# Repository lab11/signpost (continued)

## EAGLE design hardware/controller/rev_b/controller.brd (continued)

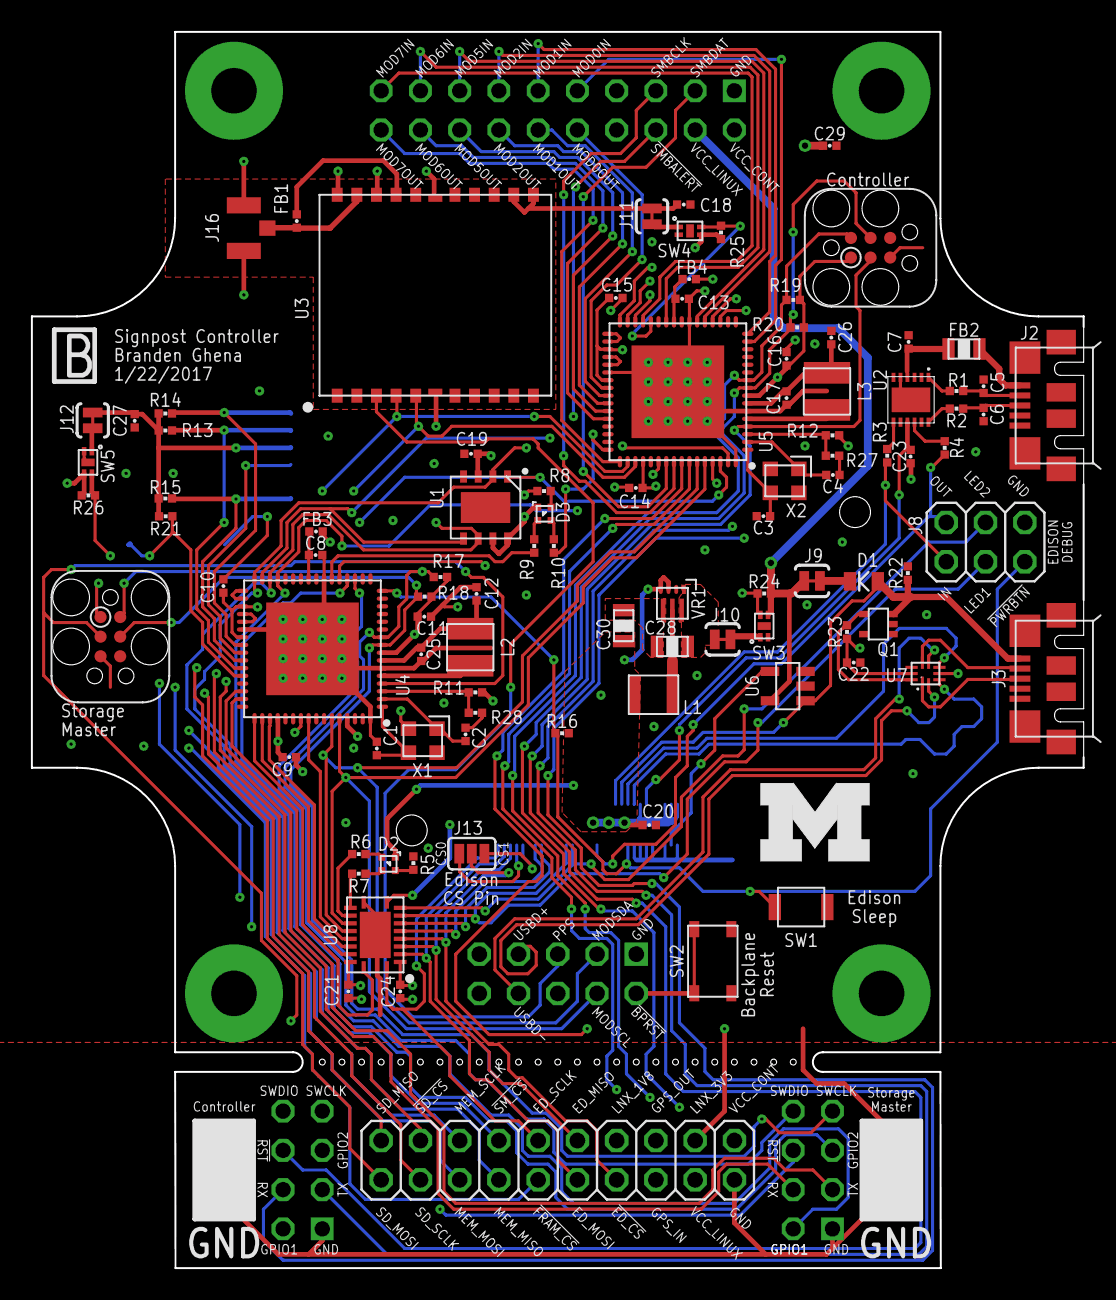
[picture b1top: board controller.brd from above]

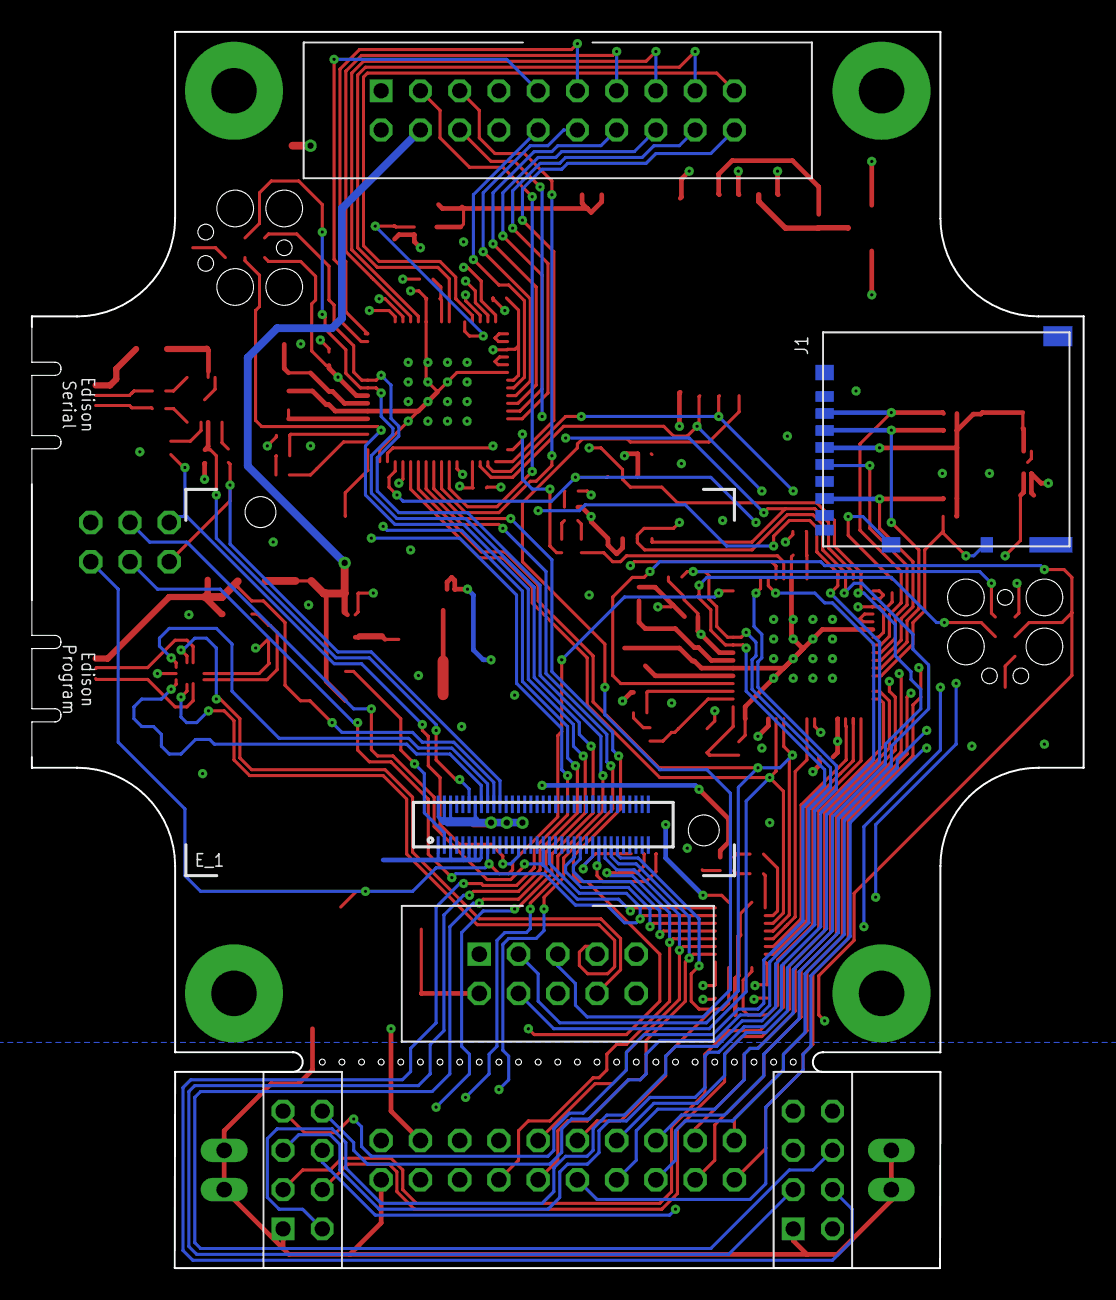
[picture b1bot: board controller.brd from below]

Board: 4 copper layers, 68.1 x 80.0 mm, 103 parts (2 on the bottom side), 123 nets.

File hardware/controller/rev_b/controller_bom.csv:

"# Bill of Materials",,,,,,,,,
"# Converted from controller_bom.xls",,,,,,,,,
"# Generated by bom_to_text.py",,,,,,,,,
"#",,,,,,,,,
Qty,Value,Device,Package,Parts,Description,AMAZON,DIGIKEY,MOUSER,NEWARK
4,8pF,CAPACITOR0402_CAP,0402_CAP,"C1, C2, C3, C4",0402 Capacitor,,490-8230-1-ND,,
2,47pF,CAPACITOR0402_CAP,0402_CAP,"C5, C6",0402 Capacitor,,490-6241-1-ND,,
1,10nF,CAPACITOR0402_CAP,0402_CAP,C7,0402 Capacitor,,490-6296-1-ND,,
17,100nF,CAPACITOR0402_CAP,0402_CAP,"C8, C9, C10, C11, C12, C13, C14, C15, C16, C17, C18, C19, C20, C21, C22, C23, C24",0402 Capacitor,,490-10777-1-ND,,
3,4.7uF,CAPACITOR0402_CAP,0402_CAP,"C25, C26, C27",0402 Capacitor,,490-13252-1-ND,,
1,10uF,CAPACITOR0805_CAP,0805_CAP,C28,0402 Capacitor,,490-8316-1-ND,,
1,10uF,CAPACITOR0402_CAP,0402_CAP,C29,0402 Capacitor,,490-13811-1-ND,,
1,22uF,CAPACITOR0805_CAP,0805_CAP,C30,0402 Capacitor,,490-1719-1-ND,,
1,DIODE,DIODE,0805_DIODE,D1,,,478-7800-1-ND,,
2,SML-LX0404SIUPGUSB,SML-LX0404SIUPGUSB,1MM_SQ_4PAD,"D2, D3",1mm^2 RGB LED,,67-2125-1-ND,,
1,EDISON_CONNECTOR_SEGMENTED,EDISON_CONNECTOR_SEGMENTED,EDISON_DAUGHTER,E_1,,B00PTVSS4A,,798-DF40HC3070DS4V51,
1,300,FERRITE_BEAD0402,0402_CAP,FB1,,,ACML-0402-301-TCT-ND,,
1,600,FERRITE_BEAD0805,0805_CAP,FB2,,,240-2390-1-ND,,
1,1.5k,FERRITE_BEAD0402,0402_CAP,FB3,,,1276-6395-1-ND,,
1,1.5k,FERRITE_BEAD0402,0402_CAP,FB4,,,1276-6395-1-ND,,
1,DM3AT-SF-PEJM5,DM3AT-SF-PEJM5,DM3AT-SF-PEJM5,J1,CONN MICRO SD R/A PUSH-PUSH SMD,,HR1964CT-ND,,
2,MICRO_USB_B_HIROSE_ZX62R-B-5P,MICRO_USB_B_HIROSE_ZX62R-B-5P,USB_MICRO_B-HIROSE-ZX62R-B-5P,"J2, J3",USB Micro B Connector,,H125274CT-ND,,
1,MODULE_CONTROLLER,MODULE_CONTROLLER,MODULE_CONTROLLER,J4,Controller module for signpost,,"S9172-ND , S9169-ND , S2221EC-04-ND , S2221EC-04-ND",,
2,,PINHD-1X2,1X02,"J5, J6",PIN HEADER,,,,
1,,PINHD-2X10,2X10,J7,PIN HEADER,,,,
1,,PINHD-2X3,2X03,J8,PIN HEADER,,,,
4,SOLDERJUMPERTRACE,SOLDERJUMPERTRACE,SJ_2S-TRACE,"J9, J10, J11, J12",Solder Jumper,,,,
1,,SOLDERJUMPER_2WAYPASTE2&3,SJ_3_PASTE2&3,J13,Solder Jumper,,,,
2,TC2030-JLINK-L,TC2030-JLINK-L,TC2030-IDC,"J14, J15",,,,,
1,U.FL-R-SMT,U.FL-R-SMT,U.FL_SMT,J16,U.FL-R-SMT Antenna Connector,,H122041-ND,,
1,0.47uH,INDUCTORDFE322512C,DFE322512C,L1,A very specific inductor,,490-10596-1-ND,81-1277AS-H-R47MP2,
1,22uH,LHQ3NP,1212,L2,LHQ3NP Inductor,,490-5350-1-ND,,
1,22uH,LHQ3NP,1212,L3,LHQ3NP Inductor,,490-5350-1-ND,,
1,UMICH_SOLID_MEDIUM,UMICH_SOLID_MEDIUM,UMICH_SOLID_200MIL,LOGO1,,,,,
1,DMN32D2LDF,DMN32D2LDF,SOT353,Q1,Common source dual n-channel mosfet,,DMN32D2LDF-7DICT-ND,,
2,27,RESISTOR0402_RES,0402_RES,"R1, R2",Resistor,,1276-3907-1-ND,,
2,100,RESISTOR0402_RES,0402_RES,"R3, R4",Resistor,,1276-3429-1-ND,,
6,1k,RESISTOR0402_RES,0402_RES,"R5, R6, R7, R8, R9, R10",Resistor,,1276-3430-1-ND,,
6,10k,RESISTOR0402_RES,0402_RES,"R11, R12, R13, R14, R15, R16",Resistor,,1276-3431-1-ND,,
5,100k,RESISTOR0402_RES,0402_RES,"R17, R18, R19, R20, R21, R22, R23",Resistor,,1276-3432-1-ND,,
3,1M,RESISTOR0402_RES,0402_RES,"R24, R25, R26",Resistor,,1276-3433-1-ND,,
2,DNP,RESISTOR0402_RES,0402_RES,"R27, R28",Resistor,,1276-3431-1-ND,,
1,B3U-1000P,B3U-1000P,B3U-1000P,SW1,Switch,,SW1020CT-ND,,
1,PTS810SJ,PTS810SJ,PTS810SJ,SW2,PTS810SJ Push Button Switch,,CKN10504CT-ND,,
3,SIP3240X,SIP3240X,TDFN4,"SW3, SW4, SW5",High power (2.4 A) high-side switch,,SIP32402ADNP-T1GE4CT-ND,,
1,FM25CLXXB-DG,FM25CLXXB-DG,TDFN-8,U1,Cypress FRAM,,FM25CL64B-DGRA-ND,,
1,FTDI234XD,FTDI234XD,DFN-12/3MM,U2,FTDI234XD USB to UART Bridge in 3x3 DFN Package,,768-1178-1-ND,895-FT234XD-R,53X3171
1,RXM-GPS-RM-T,RXM-GPS-RM-T,RXM-GPS-RM-T,U3,The RM Series GPS receiver module is a,,RXM-GPS-RM-TCT-ND,,
2,SAM4LC8BA,SAM4LC8BA,QFN-64-9MM,"U4, U5",SAM4L Microcontroller. 64QFN Package. 512 Flash.,,ATSAM4LC8BA-MURCT-ND,,
1,SN74LVC1G125DBVR,SN74LVC1G125DBVR,SOT-23-5,U6,Single Bus Buffer Gate with 3-state output,,296-11603-1-nd,,
1,TS3USB30E,TS3USB30E,UQFN-10,U7,USB Mux with OE control and ESD,,296-24684-1-ND,,
1,TXS0108EVQFN20,TXS0108EVQFN20,R-PVQFN-N20,U8,TXS0108E 8-Bit Bi-directional Voltage Translator,,296-24806-1-ND,,
1,TPS62086,TPS62086,RLT0007A,VR1,Buck Switching Regulator IC Positive Fixed 3.3V 1 Output 3A 7-VFDFN,,296-40831-1-ND,,
2,16MHz,FH1600015,FHXXX,"X1, X2",Pericom Type FH 16 MHz 2.5 x 2.0 mm,,FH1600015CT-ND,,

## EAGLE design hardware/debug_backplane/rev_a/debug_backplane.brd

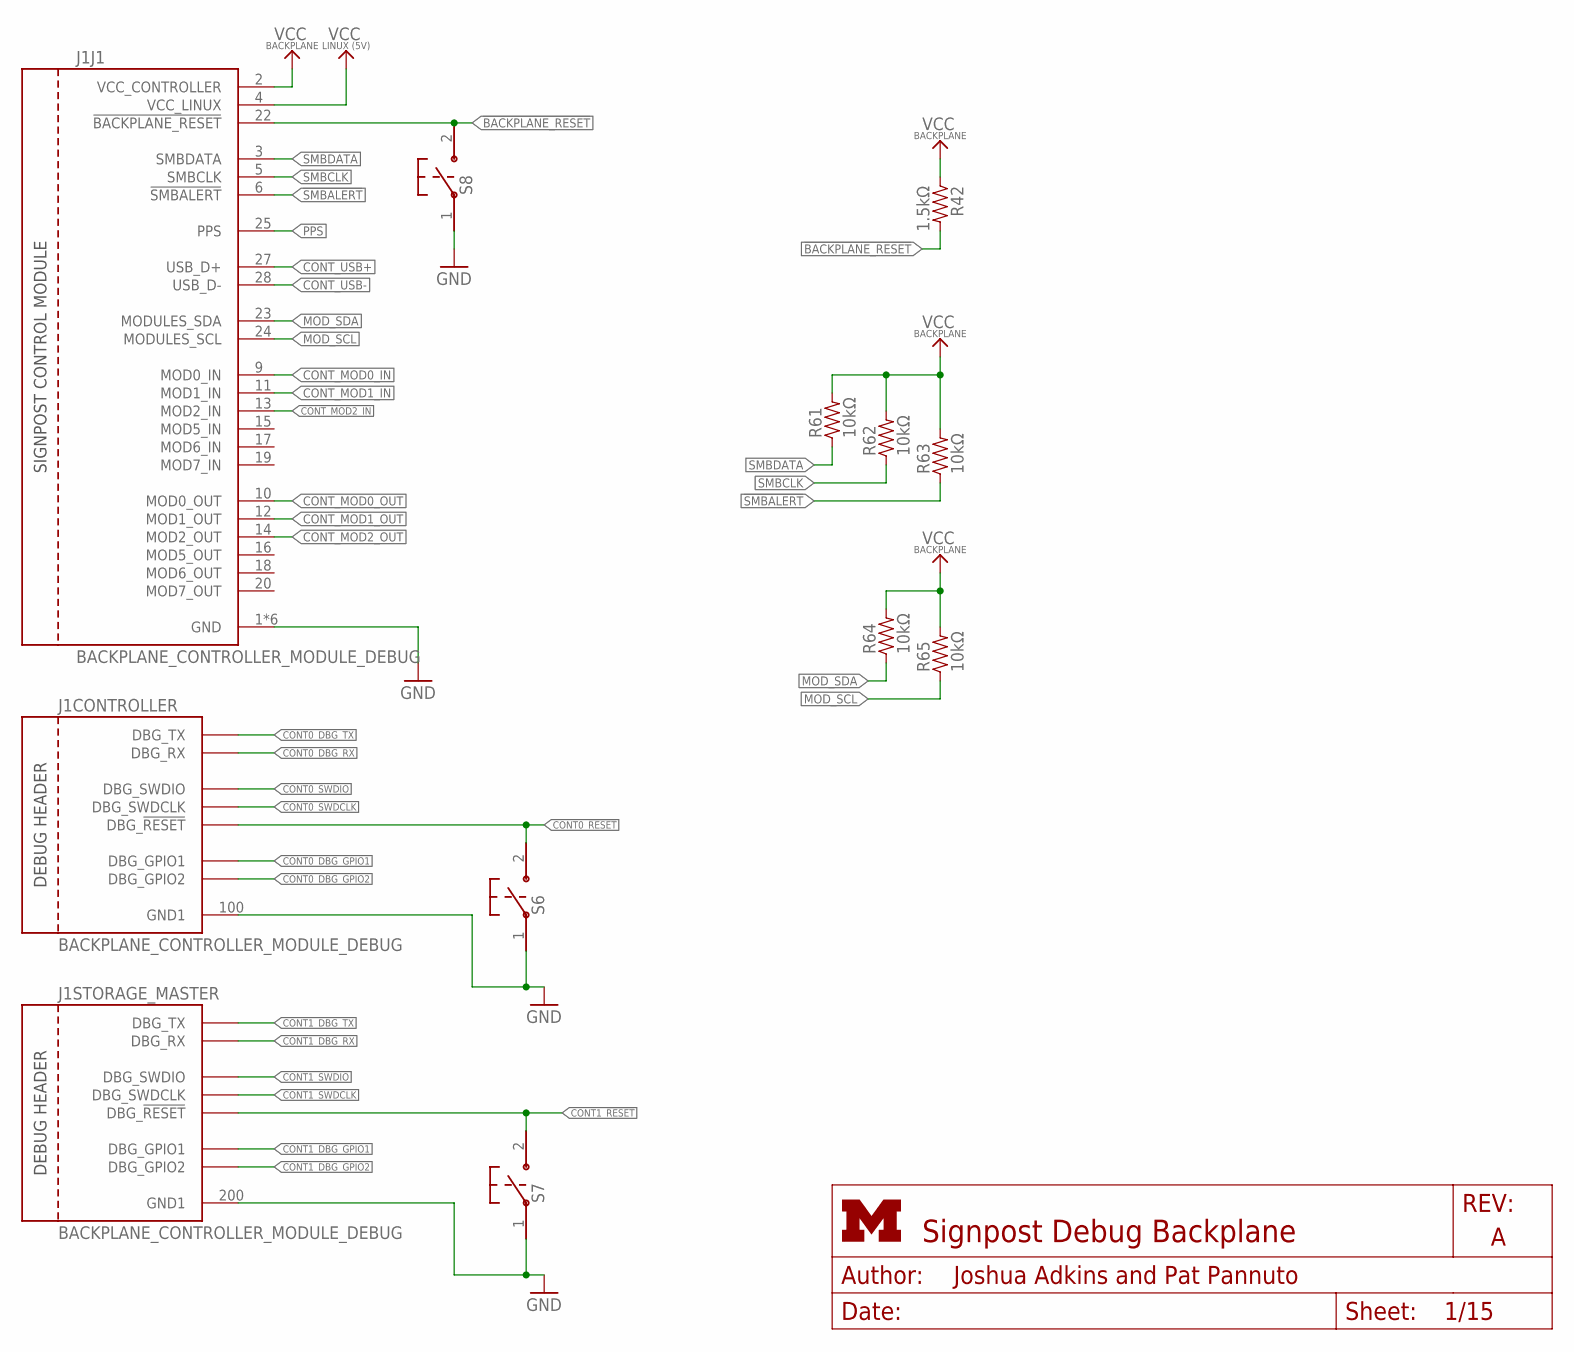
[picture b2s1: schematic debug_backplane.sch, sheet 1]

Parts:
J1: BACKPLANE_CONTROLLER_MODULE_DEBUG; BACKPLANE_MODULE_20PIN_10PIN_DEBUG
R42: 1.5kΩ; 0603-RES
R61, R62, R63, R64, R65: 10kΩ; 0603-RES
S6, S7, S8: B3U-1000P

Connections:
!BACKPLANE_RESET: J1.22 (!BACKPLANE_RESET), R42.2, S8.2; also elsewhere on the board
!SMBALERT: J1.6 (!SMBALERT), R63.1; also elsewhere on the board
CONT0_!RESET: J1.105 (DBG_!RESET), S6.2; also elsewhere on the board
CONT0_DBG_GPIO1: J1.101 (DBG_GPIO1); also elsewhere on the board
CONT0_DBG_GPIO2: J1.104 (DBG_GPIO2); also elsewhere on the board
CONT0_DBG_RX: J1.103 (DBG_RX); also elsewhere on the board
CONT0_DBG_TX: J1.102 (DBG_TX); also elsewhere on the board
CONT0_SWDCLK: J1.106 (DBG_SWDCLK); also elsewhere on the board
CONT0_SWDIO: J1.107 (DBG_SWDIO); also elsewhere on the board
CONT1_!RESET: J1.205 (DBG_!RESET), S7.2; also elsewhere on the board
CONT1_DBG_GPIO1: J1.201 (DBG_GPIO1); also elsewhere on the board
CONT1_DBG_GPIO2: J1.204 (DBG_GPIO2); also elsewhere on the board
CONT1_DBG_RX: J1.203 (DBG_RX); also elsewhere on the board
CONT1_DBG_TX: J1.202 (DBG_TX); also elsewhere on the board
CONT1_SWDCLK: J1.206 (DBG_SWDCLK); also elsewhere on the board
CONT1_SWDIO: J1.207 (DBG_SWDIO); also elsewhere on the board
CONT_MOD0_IN: J1.9 (MOD0_IN); also elsewhere on the board
CONT_MOD0_OUT: J1.10 (MOD0_OUT); also elsewhere on the board
CONT_MOD1_IN: J1.11 (MOD1_IN); also elsewhere on the board
CONT_MOD1_OUT: J1.12 (MOD1_OUT); also elsewhere on the board
CONT_MOD2_IN: J1.13 (MOD2_IN); also elsewhere on the board
CONT_MOD2_OUT: J1.14 (MOD2_OUT); also elsewhere on the board
CONT_USB+: J1.27 (USB_D+); also elsewhere on the board
CONT_USB-: J1.28 (USB_D-); also elsewhere on the board
GND: J1.1 (GND), J1.21 (GND), J1.100 (GND1), J1.200 (GND1), J1.MNT1 (GND), J1.MNT2 (GND), J1.MNT3 (GND), J1.MNT4 (GND), S6.1, S7.1, S8.1; also elsewhere on the board
MOD_SCL: J1.24 (MODULES_SCL), R65.1; also elsewhere on the board
MOD_SDA: J1.23 (MODULES_SDA), R64.1; also elsewhere on the board
PPS: J1.25 (PPS); also elsewhere on the board
SMBCLK: J1.5 (SMBCLK), R62.1; also elsewhere on the board
SMBDATA: J1.3 (SMBDATA), R61.1; also elsewhere on the board
VCC_BACKPLANE: J1.2 (VCC_CONTROLLER), R42.1, R61.2, R62.2, R63.2, R64.2, R65.2; also elsewhere on the board
VCC_LINUX: J1.4 (VCC_LINUX); also elsewhere on the board

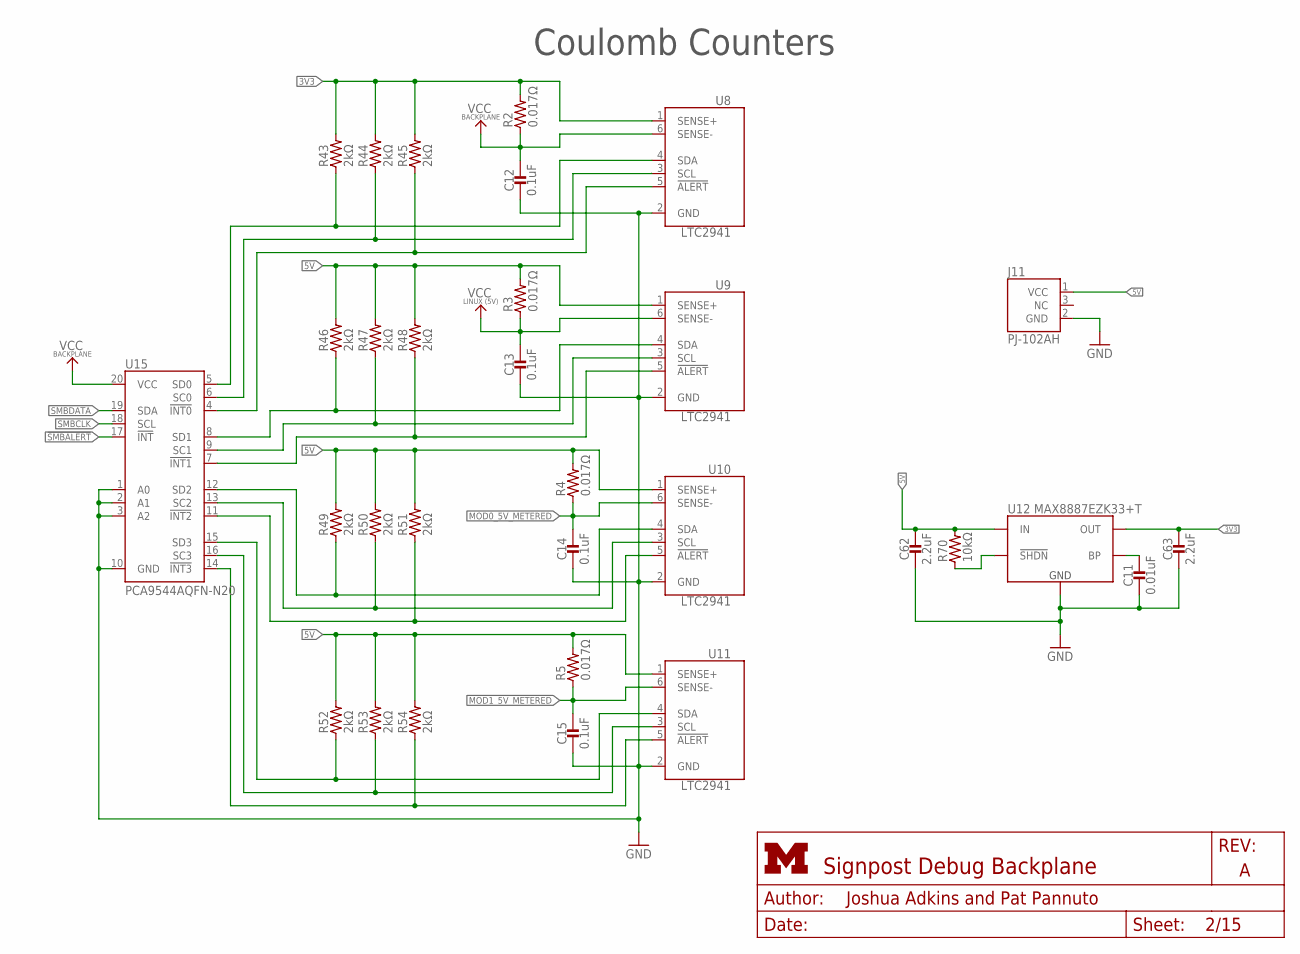
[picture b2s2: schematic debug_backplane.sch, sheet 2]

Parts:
C11: 0.01uF; 0402_CAP
C12, C13, C14, C15: 0.1uF; 0402_CAP
C62, C63: 2.2uF; 0603_CAP
J11: PJ-102AH
R2, R3, R4, R5: 0.017Ω; 0805_RES
R43, R44, R45, R46, R47, R48, R49, R50, R51, R52, R53, R54: 2kΩ; 0402_RES
R70: 10kΩ; 0603-RES
U8, U9, U10, U11: LTC2941; DFN-6-2MMX3MM
U12: MAX8887EZK33+T; SOT-23-5
U15: PCA9544AQFN-N20; QFN-N20

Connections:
3V3: C63.1, R2.2, R43.2, R44.2, R45.2, U8.1 (SENSE+), U12.5 (OUT); also elsewhere on the board
5V: C62.1, J11.1 (VCC), R3.2, R4.2, R5.2, R46.2, R47.2, R48.2, R49.2, R50.2, R51.2, R52.2, R53.2, R54.2, R70.2, U9.1 (SENSE+), U10.1 (SENSE+), U11.1 (SENSE+), U12.1 (IN); also elsewhere on the board
!SMBALERT: U15.17 (!INT); also elsewhere on the board
GND: C11.2, C12.2, C13.2, C14.2, C15.2, C62.2, C63.2, J11.2 (GND), U8.2 (GND), U9.2 (GND), U10.2 (GND), U11.2 (GND), U12.2 (GND), U15.1 (A0), U15.2 (A1), U15.3 (A2), U15.10 (GND); also elsewhere on the board
MOD0_5V_METERED: C14.1, R4.1, U10.6 (SENSE-); also elsewhere on the board
MOD1_5V_METERED: C15.1, R5.1, U11.6 (SENSE-); also elsewhere on the board
unnamed: R70.1, U12.3 (!SHDN)
unnamed: C11.1, U12.4 (BP)
unnamed: R43.1, U8.4 (SDA), U15.5 (SD0)
unnamed: R44.1, U8.3 (SCL), U15.6 (SC0)
unnamed: R49.1, U10.4 (SDA), U15.12 (SD2)
unnamed: R50.1, U10.3 (SCL), U15.13 (SC2)
unnamed: R51.1, U10.5 (!ALERT), U15.11 (!INT2)
unnamed: R52.1, U11.4 (SDA), U15.15 (SD3)
unnamed: R53.1, U11.3 (SCL), U15.16 (SC3)
unnamed: R54.1, U11.5 (!ALERT), U15.14 (!INT3)
unnamed: R45.1, U8.5 (!ALERT), U15.4 (!INT0)
unnamed: R46.1, U9.4 (SDA), U15.8 (SD1)
unnamed: R47.1, U9.3 (SCL), U15.9 (SC1)
unnamed: R48.1, U9.5 (!ALERT), U15.7 (!INT1)
SMBCLK: U15.18 (SCL); also elsewhere on the board
SMBDATA: U15.19 (SDA); also elsewhere on the board
VCC_BACKPLANE: C12.1, R2.1, U8.6 (SENSE-), U15.20 (VCC); also elsewhere on the board
VCC_LINUX: C13.1, R3.1, U9.6 (SENSE-); also elsewhere on the board

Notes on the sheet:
Coulomb Counters

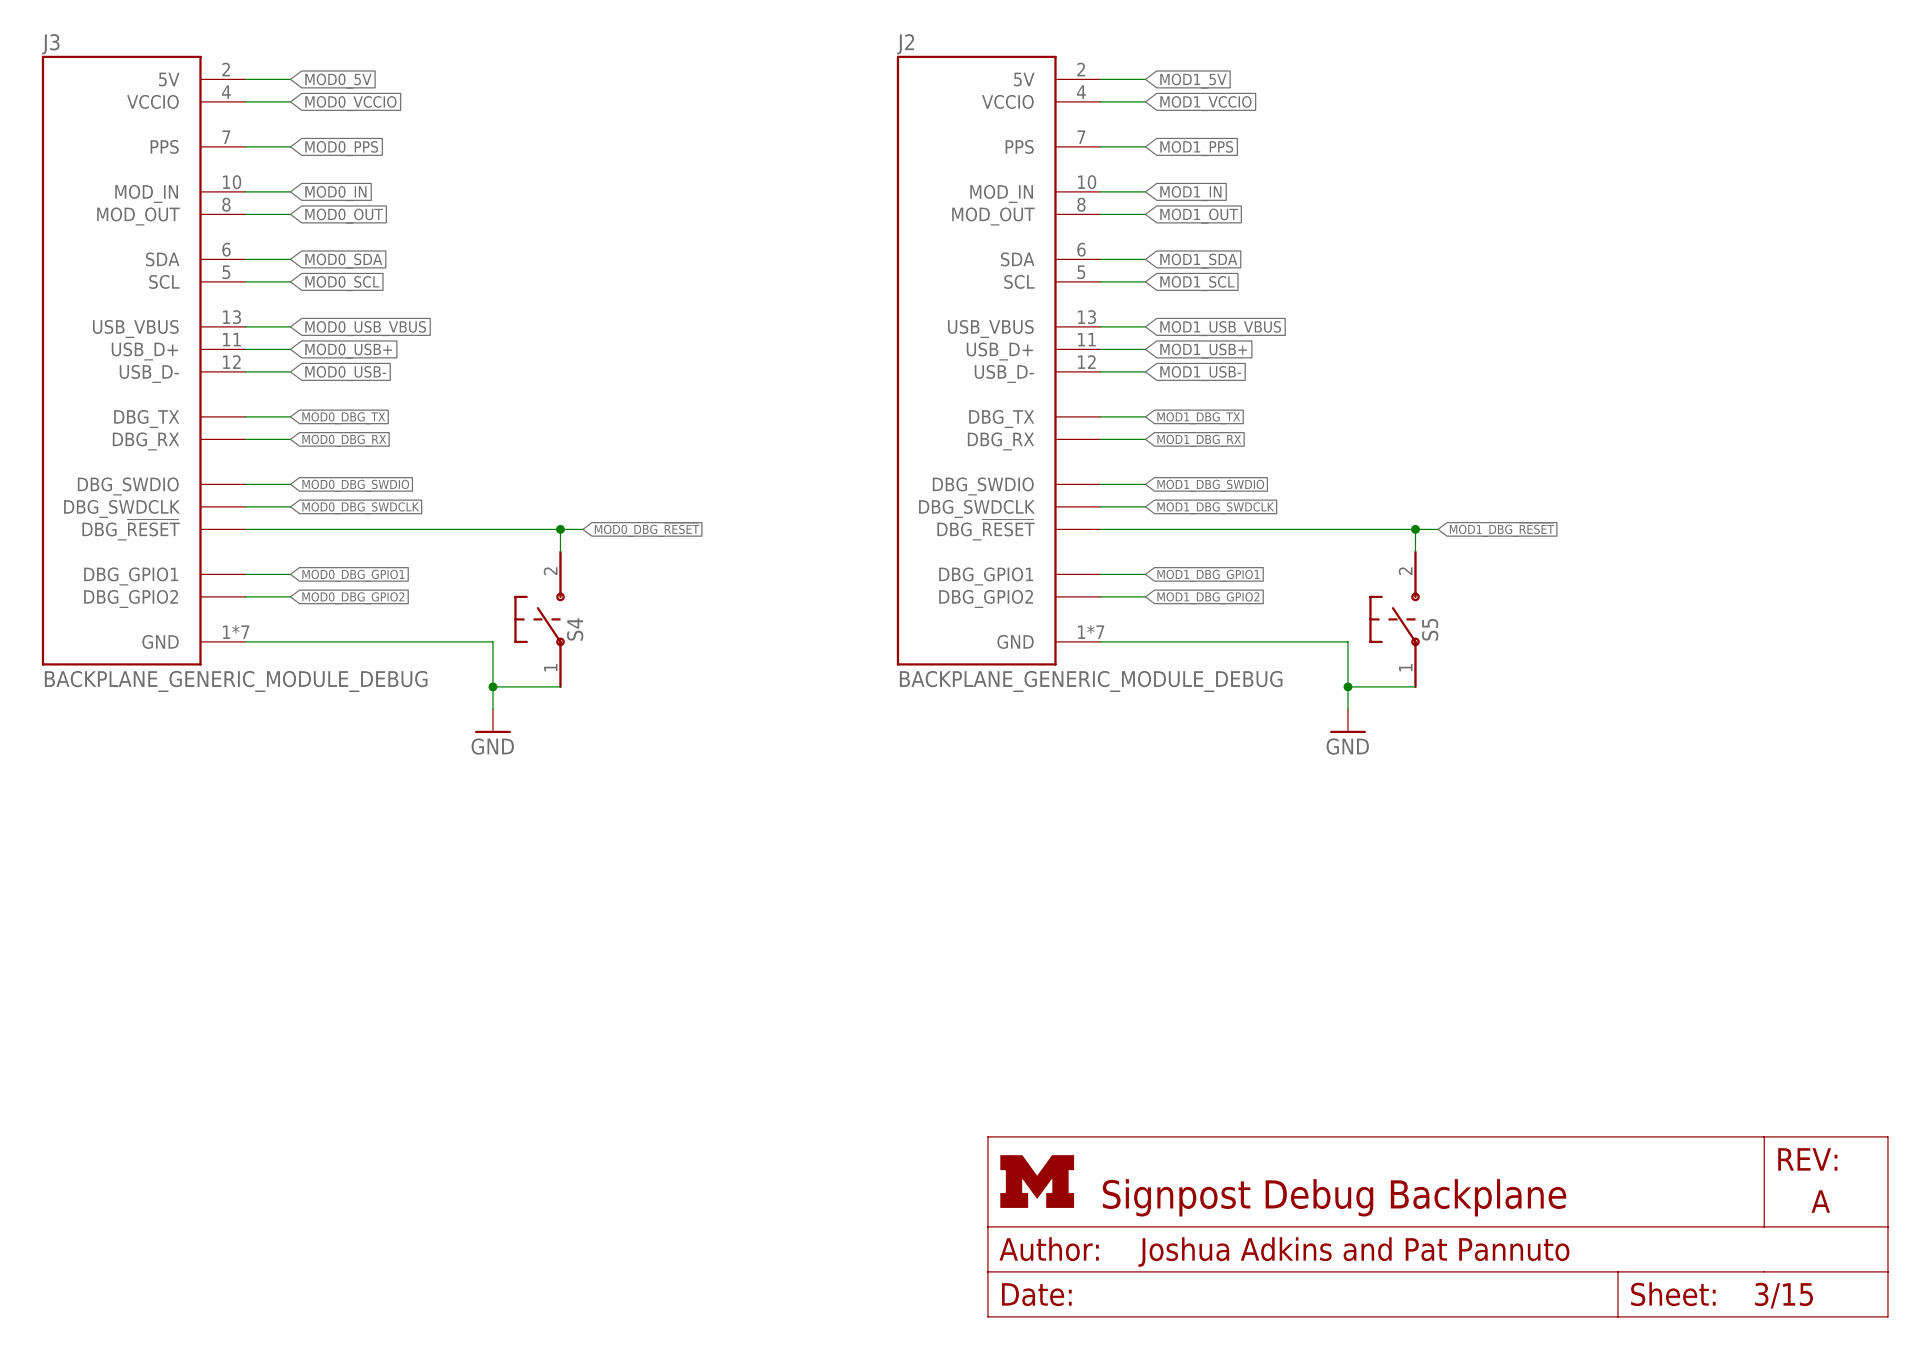
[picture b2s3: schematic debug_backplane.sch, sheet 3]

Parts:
J2, J3: BACKPLANE_GENERIC_MODULE_DEBUG; BACKPLANE_MODULE_14PIN_8PIN
S4, S5: B3U-1000P

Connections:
GND: J2.1 (GND), J2.14 (GND), J2.15 (GND), J2.MNT1 (GND), J2.MNT2 (GND), J2.MNT3 (GND), J2.MNT4 (GND), J3.1 (GND), J3.14 (GND), J3.15 (GND), J3.MNT1 (GND), J3.MNT2 (GND), J3.MNT3 (GND), J3.MNT4 (GND), S4.1, S5.1; also elsewhere on the board
MOD0_5V: J3.2 (5V); also elsewhere on the board
MOD0_DBG_!RESET: J3.20 (DBG_!RESET), S4.2; also elsewhere on the board
MOD0_DBG_GPIO1: J3.16 (DBG_GPIO1); also elsewhere on the board
MOD0_DBG_GPIO2: J3.19 (DBG_GPIO2); also elsewhere on the board
MOD0_DBG_RX: J3.18 (DBG_RX); also elsewhere on the board
MOD0_DBG_SWDCLK: J3.21 (DBG_SWDCLK); also elsewhere on the board
MOD0_DBG_SWDIO: J3.22 (DBG_SWDIO); also elsewhere on the board
MOD0_DBG_TX: J3.17 (DBG_TX); also elsewhere on the board
MOD0_IN: J3.10 (MOD_IN); also elsewhere on the board
MOD0_OUT: J3.8 (MOD_OUT); also elsewhere on the board
MOD0_PPS: J3.7 (PPS); also elsewhere on the board
MOD0_SCL: J3.5 (SCL); also elsewhere on the board
MOD0_SDA: J3.6 (SDA); also elsewhere on the board
MOD0_USB+: J3.11 (USB_D+); also elsewhere on the board
MOD0_USB-: J3.12 (USB_D-); also elsewhere on the board
MOD0_USB_VBUS: J3.13 (USB_VBUS); also elsewhere on the board
MOD0_VCCIO: J3.4 (VCCIO); also elsewhere on the board
MOD1_5V: J2.2 (5V); also elsewhere on the board
MOD1_DBG_!RESET: J2.20 (DBG_!RESET), S5.2; also elsewhere on the board
MOD1_DBG_GPIO1: J2.16 (DBG_GPIO1); also elsewhere on the board
MOD1_DBG_GPIO2: J2.19 (DBG_GPIO2); also elsewhere on the board
MOD1_DBG_RX: J2.18 (DBG_RX); also elsewhere on the board
MOD1_DBG_SWDCLK: J2.21 (DBG_SWDCLK); also elsewhere on the board
MOD1_DBG_SWDIO: J2.22 (DBG_SWDIO); also elsewhere on the board
MOD1_DBG_TX: J2.17 (DBG_TX); also elsewhere on the board
MOD1_IN: J2.10 (MOD_IN); also elsewhere on the board
MOD1_OUT: J2.8 (MOD_OUT); also elsewhere on the board
MOD1_PPS: J2.7 (PPS); also elsewhere on the board
MOD1_SCL: J2.5 (SCL); also elsewhere on the board
MOD1_SDA: J2.6 (SDA); also elsewhere on the board
MOD1_USB+: J2.11 (USB_D+); also elsewhere on the board
MOD1_USB-: J2.12 (USB_D-); also elsewhere on the board
MOD1_USB_VBUS: J2.13 (USB_VBUS); also elsewhere on the board
MOD1_VCCIO: J2.4 (VCCIO); also elsewhere on the board

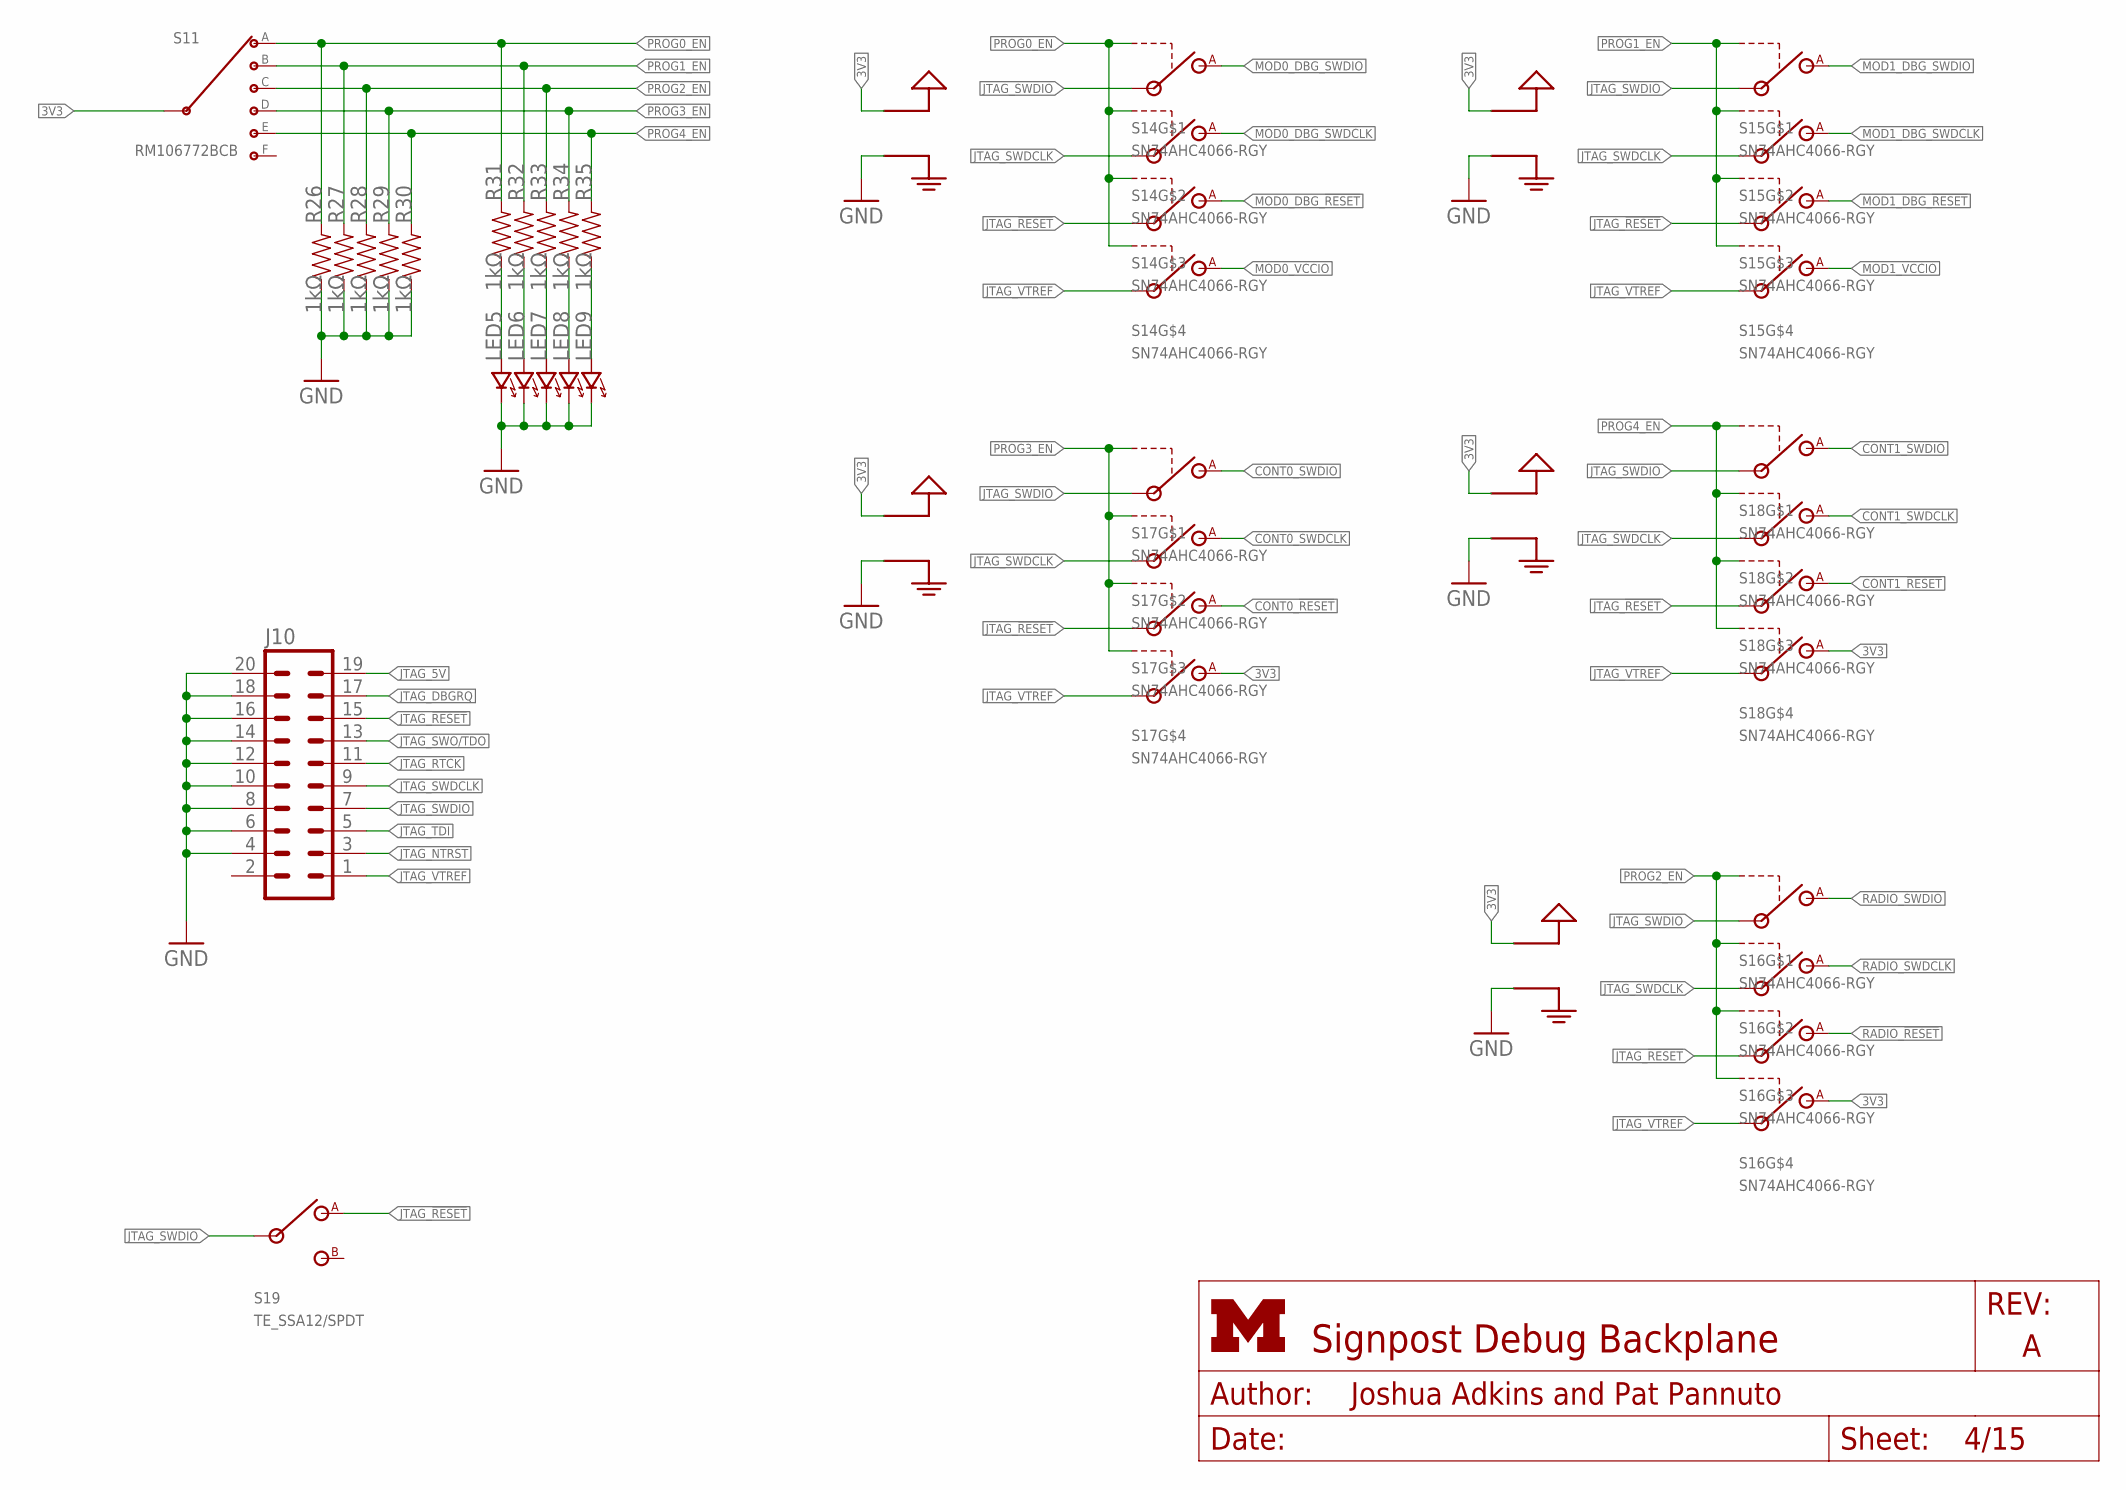
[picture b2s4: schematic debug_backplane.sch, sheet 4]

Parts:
J10: ML20
LED5, LED6, LED7, LED8, LED9: LED0603; LED-0603
R26, R27, R28, R29, R30, R31, R32, R33, R34, R35: 1kΩ; 0603-RES
S11: RM106772BCB; RM-SWITCH
S14, S15, S16, S17, S18: SN74AHC4066-RGY; S-PVQFN-N14-3.5MM
S19: TE_SSA12/SPDT

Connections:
3V3: S11.C (INPUT), S14.14 (VCC), S15.14 (VCC), S16.10 (A), S16.14 (VCC), S17.10 (A), S17.14 (VCC), S18.10 (A), S18.14 (VCC); also elsewhere on the board
CONT0_!RESET: S17.9 (A); also elsewhere on the board
CONT0_SWDCLK: S17.3 (A); also elsewhere on the board
CONT0_SWDIO: S17.2 (A); also elsewhere on the board
CONT1_!RESET: S18.9 (A); also elsewhere on the board
CONT1_SWDCLK: S18.3 (A); also elsewhere on the board
CONT1_SWDIO: S18.2 (A); also elsewhere on the board
GND: J10.4, J10.6, J10.8, J10.10, J10.12, J10.14, J10.16, J10.18, J10.20, LED5.C (CATHODE), LED6.C (CATHODE), LED7.C (CATHODE), LED8.C (CATHODE), LED9.C (CATHODE), R26.1, R27.1, R28.1, R29.1, R30.1, S14.7 (GND), S15.7 (GND), S16.7 (GND), S17.7 (GND), S18.7 (GND); also elsewhere on the board
JTAG_5V: J10.19
JTAG_!RESET: J10.15, S14.8 (IN), S15.8 (IN), S16.8 (IN), S17.8 (IN), S18.8 (IN), S19.1 (A)
JTAG_DBGRQ: J10.17
JTAG_NTRST: J10.3
JTAG_RTCK: J10.11
JTAG_SWDCLK: J10.9, S14.4 (IN), S15.4 (IN), S16.4 (IN), S17.4 (IN), S18.4 (IN)
JTAG_SWDIO: J10.7, S14.1 (IN), S15.1 (IN), S16.1 (IN), S17.1 (IN), S18.1 (IN), S19.IN
JTAG_SWO/TDO: J10.13
JTAG_TDI: J10.5
JTAG_VTREF: J10.1, S14.11 (IN), S15.11 (IN), S16.11 (IN), S17.11 (IN), S18.11 (IN)
MOD0_DBG_!RESET: S14.9 (A); also elsewhere on the board
MOD0_DBG_SWDCLK: S14.3 (A); also elsewhere on the board
MOD0_DBG_SWDIO: S14.2 (A); also elsewhere on the board
MOD0_VCCIO: S14.10 (A); also elsewhere on the board
MOD1_DBG_!RESET: S15.9 (A); also elsewhere on the board
MOD1_DBG_SWDCLK: S15.3 (A); also elsewhere on the board
MOD1_DBG_SWDIO: S15.2 (A); also elsewhere on the board
MOD1_VCCIO: S15.10 (A); also elsewhere on the board
unnamed: LED6.A (ANODE), R32.1
unnamed: LED5.A (ANODE), R31.1
unnamed: LED7.A (ANODE), R33.1
unnamed: LED8.A (ANODE), R34.1
unnamed: LED9.A (ANODE), R35.1
PROG0_EN: R26.2, R31.2, S11.1 (A), S14.5 (CTRL), S14.6 (CTRL), S14.12 (CTRL), S14.13 (CTRL)
PROG1_EN: R27.2, R32.2, S11.2 (B), S15.5 (CTRL), S15.6 (CTRL), S15.12 (CTRL), S15.13 (CTRL)
PROG2_EN: R28.2, R33.2, S11.3 (C), S16.5 (CTRL), S16.6 (CTRL), S16.12 (CTRL), S16.13 (CTRL)
PROG3_EN: R29.2, R34.2, S11.4 (D), S17.5 (CTRL), S17.6 (CTRL), S17.12 (CTRL), S17.13 (CTRL)
PROG4_EN: R30.2, R35.2, S11.5 (E), S18.5 (CTRL), S18.6 (CTRL), S18.12 (CTRL), S18.13 (CTRL)
RADIO_!RESET: S16.9 (A); also elsewhere on the board
RADIO_SWDCLK: S16.3 (A); also elsewhere on the board
RADIO_SWDIO: S16.2 (A); also elsewhere on the board

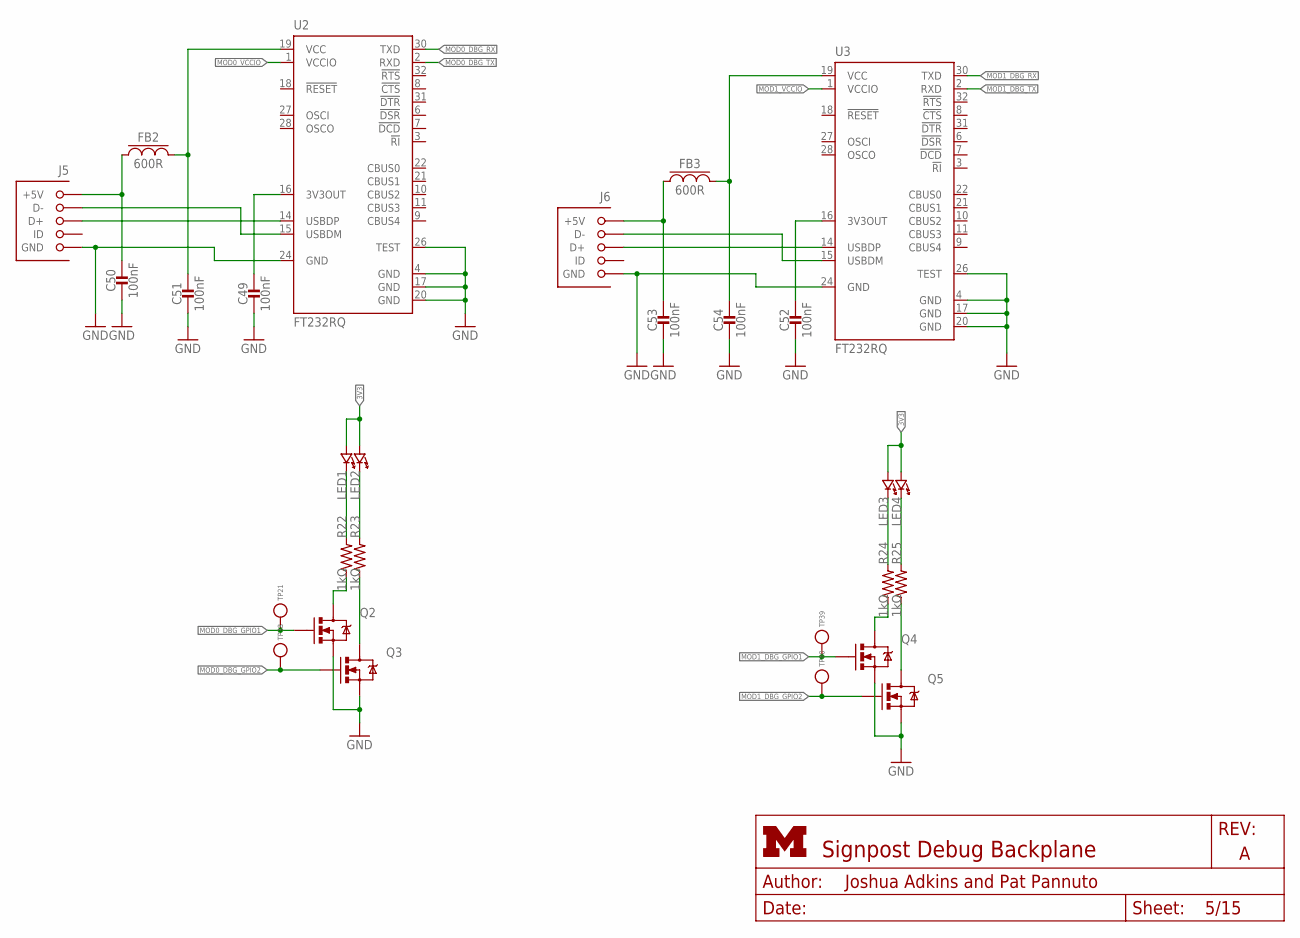
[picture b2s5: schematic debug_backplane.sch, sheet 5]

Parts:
C49, C50, C51, C52, C53, C54: 100nF; 0603_CAP
FB2, FB3: 600R; 0603_CAP
J5, J6: MICRO_USB_B_HIROSE_ZX62R-B-5P; USB_MICRO_B-HIROSE-ZX62R-B-5P
LED1, LED2, LED3, LED4: LED0603; LED-0603
Q2, Q3, Q4, Q5: MOSFET-NCHANNELSMD; SOT23-3
R22, R23, R24, R25: 1kΩ; 0603-RES
TP21, TP38, TP39, TP40: TEST_POINT_0.040IN; TESTPOINT_0.040IN
U2, U3: FT232RQ; QFN32

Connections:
3V3: LED1.A (ANODE), LED2.A (ANODE), LED3.A (ANODE), LED4.A (ANODE); also elsewhere on the board
GND: C49.2, C50.2, C51.2, C52.2, C53.2, C54.2, J5.5 (GND), J6.5 (GND), Q2.2 (S), Q3.2 (S), Q4.2 (S), Q5.2 (S), U2.4 (GND), U2.17 (GND), U2.20 (GND), U2.24 (GND), U2.26 (TEST), U3.4 (GND), U3.17 (GND), U3.20 (GND), U3.24 (GND), U3.26 (TEST); also elsewhere on the board
MOD0_DBG_GPIO1: Q2.1 (G), TP21.TESTPOINT; also elsewhere on the board
MOD0_DBG_GPIO2: Q3.1 (G), TP38.TESTPOINT; also elsewhere on the board
MOD0_DBG_RX: U2.30 (TXD); also elsewhere on the board
MOD0_DBG_TX: U2.2 (RXD); also elsewhere on the board
MOD0_VCCIO: U2.1 (VCCIO); also elsewhere on the board
MOD1_DBG_GPIO1: Q4.1 (G), TP39.TESTPOINT; also elsewhere on the board
MOD1_DBG_GPIO2: Q5.1 (G), TP40.TESTPOINT; also elsewhere on the board
MOD1_DBG_RX: U3.30 (TXD); also elsewhere on the board
MOD1_DBG_TX: U3.2 (RXD); also elsewhere on the board
MOD1_VCCIO: U3.1 (VCCIO); also elsewhere on the board
unnamed: LED1.C (CATHODE), R22.2
unnamed: LED2.C (CATHODE), R23.2
unnamed: Q2.3 (D), R22.1
unnamed: Q3.3 (D), R23.1
unnamed: LED3.C (CATHODE), R24.2
unnamed: LED4.C (CATHODE), R25.2
unnamed: Q4.3 (D), R24.1
unnamed: Q5.3 (D), R25.1
unnamed: J5.2 (D-), U2.15 (USBDM)
unnamed: J5.3 (D+), U2.14 (USBDP)
unnamed: C50.1, FB2.1, J5.1 (+5V)
unnamed: C51.1, FB2.2, U2.19 (VCC)
unnamed: C49.1, U2.16 (3V3OUT)
unnamed: J6.2 (D-), U3.15 (USBDM)
unnamed: J6.3 (D+), U3.14 (USBDP)
unnamed: C53.1, FB3.1, J6.1 (+5V)
unnamed: C54.1, FB3.2, U3.19 (VCC)
unnamed: C52.1, U3.16 (3V3OUT)
